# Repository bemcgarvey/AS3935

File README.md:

# AS3935  
 
A lightning detector using the AS3935 chip from AMS

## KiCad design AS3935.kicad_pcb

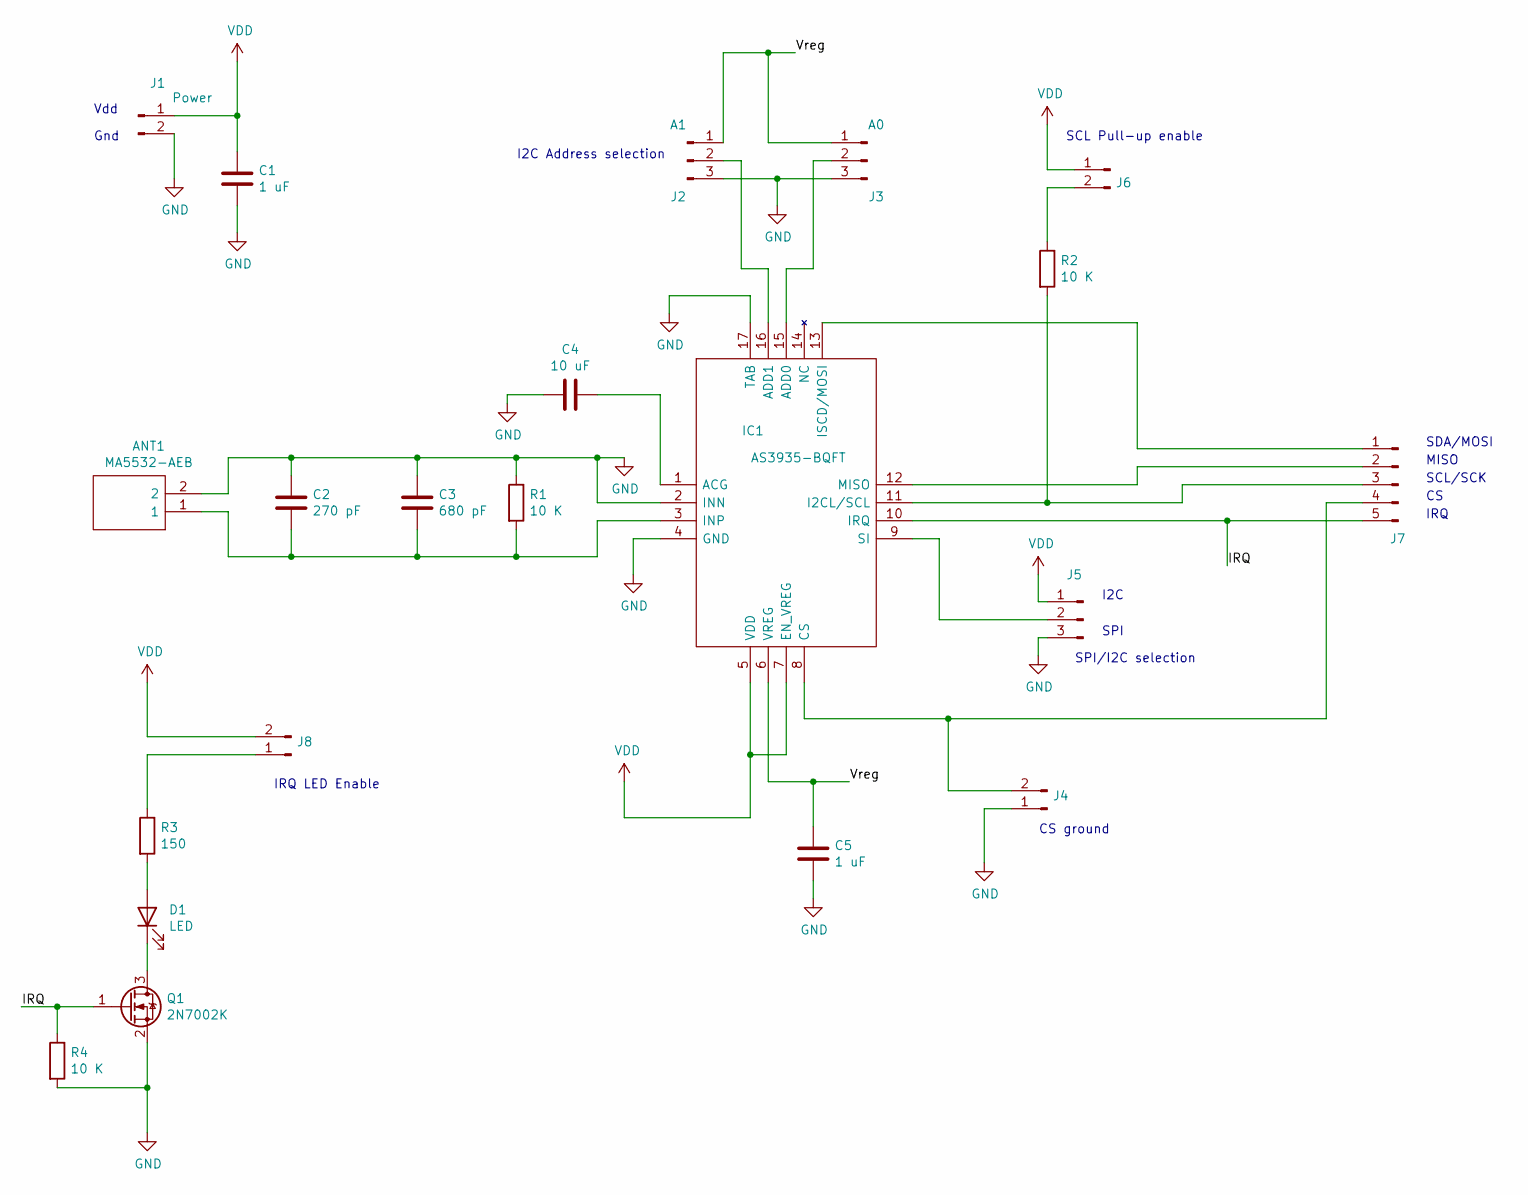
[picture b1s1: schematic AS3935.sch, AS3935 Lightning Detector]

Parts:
ANT1: MA5532-AEB; MA5532; Mouser Part Number 994-MA5532-AE
C1, C5: 1 uF; C_0603_1608Metric
C2: 270 pF; C_0603_1608Metric
C3: 680 pF; C_0603_1608Metric
C4: 10 uF; C_0603_1608Metric
D1: LED; LED_0805_2012Metric_Castellated
IC1: AS3935-BQFT; QFN65P400X400X80-17N; Mouser Part Number 985-AS3935-BQFT
J1: Power; PinHeader_1x02_P2.54mm_Vertical
J2: A1; PinHeader_1x03_P2.54mm_Vertical
J3: A0; PinHeader_1x03_P2.54mm_Vertical
J4, J6, J8: Conn_01x02_Male; PinHeader_1x02_P2.54mm_Vertical
J5: Conn_01x03_Male; PinHeader_1x03_P2.54mm_Vertical
J7: Conn_01x05_Male; PinHeader_1x05_P2.54mm_Vertical
Q1: 2N7002K; SOT-23
R1, R2, R4: 10 K; R_0603_1608Metric
R3: 150; R_0603_1608Metric

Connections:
/IRQ: IC1.10 (IRQ), J7.5, Q1.1 (G), R4.1
/Vreg: C5.1, IC1.6 (VREG), J2.1, J3.1
GND: ANT1.2, C1.2, C2.1, C3.1, C4.1, C5.2, IC1.2 (INN), IC1.4 (GND), IC1.17 (TAB), J1.2, J2.3, J3.3, J4.1, J5.3, Q1.2 (S), R1.1, R4.2
unnamed: ANT1.1, C2.2, C3.2, IC1.3 (INP), R1.2
unnamed: C4.2, IC1.1 (ACG)
unnamed: D1.1 (K), Q1.3 (D)
unnamed: D1.2 (A), R3.2
unnamed: IC1.8 (CS), J4.2, J7.4
unnamed: IC1.9 (SI), J5.2
unnamed: IC1.11 (I2CL/SCL), J7.3, R2.2
unnamed: IC1.12 (MISO), J7.2
unnamed: IC1.13 (ISCD/MOSI), J7.1
unnamed: IC1.15 (ADD0), J3.2
unnamed: IC1.16 (ADD1), J2.2
unnamed: J6.2, R2.1
unnamed: J8.1, R3.1
VDD: C1.1, IC1.5 (VDD), IC1.7 (EN_VREG), J1.1, J5.1, J6.1, J8.2

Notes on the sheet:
Vdd
Gnd
I2C Address selection
SCL Pull-up enable
CS ground
SPI/I2C selection
SDA/MOSI
MISO
SCL/SCK
IRQ
SPI
I2C
IRQ LED Enable

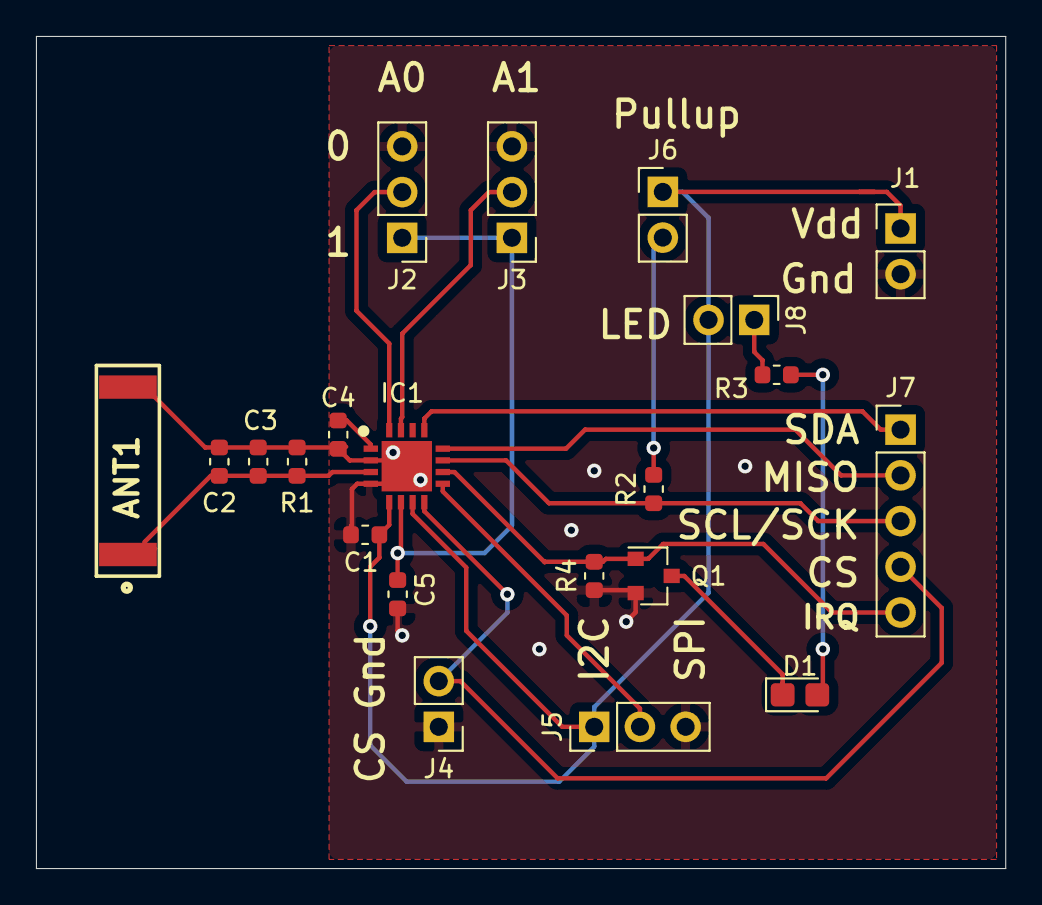
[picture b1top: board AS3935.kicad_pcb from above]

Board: 2 copper layers, 53.8 x 46.2 mm, 21 parts (0 on the bottom side), 17 nets.

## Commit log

2020-03-14 Added datasheet
2020-03-14 Added IRQ LED
2020-04-03 Added JLC serial
2021-02-15 Adjusted pcb properties
    Regenerated gerbers
2021-02-18 Final pcb
2021-04-12 Initial Arduino and PIC projects
2021-04-12 I2C working
2021-04-13 SPI working
2021-04-14 Working PIC firmware
2021-04-14 Improved tuning
2021-04-14 Changed timer used for tuning
2021-04-15 Added dynamic sensitivity adjustments
2021-04-15 Added C2 comment
    The first populated board worked better with 330 pF for C2
2021-04-15 Minor fixes
2021-04-18 Fixed clearStats(), added readEnergy()
